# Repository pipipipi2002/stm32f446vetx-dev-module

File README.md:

# STM32F446VETx Develpoment Module

This repository contains the hardware files and firmware for basic bringup of the module as well as basic testing script.

- [Interactive BOM](https://pipipipi2002.github.io/stm32f446vetx-dev-module/hardware/STM32F446VE-Module/output/interactive_bom.html)

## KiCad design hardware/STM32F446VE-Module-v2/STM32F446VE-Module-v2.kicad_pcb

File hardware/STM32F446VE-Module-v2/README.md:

# Changelog from V1
- Flip CAN_RX and CAN_TX to TCAN332GD

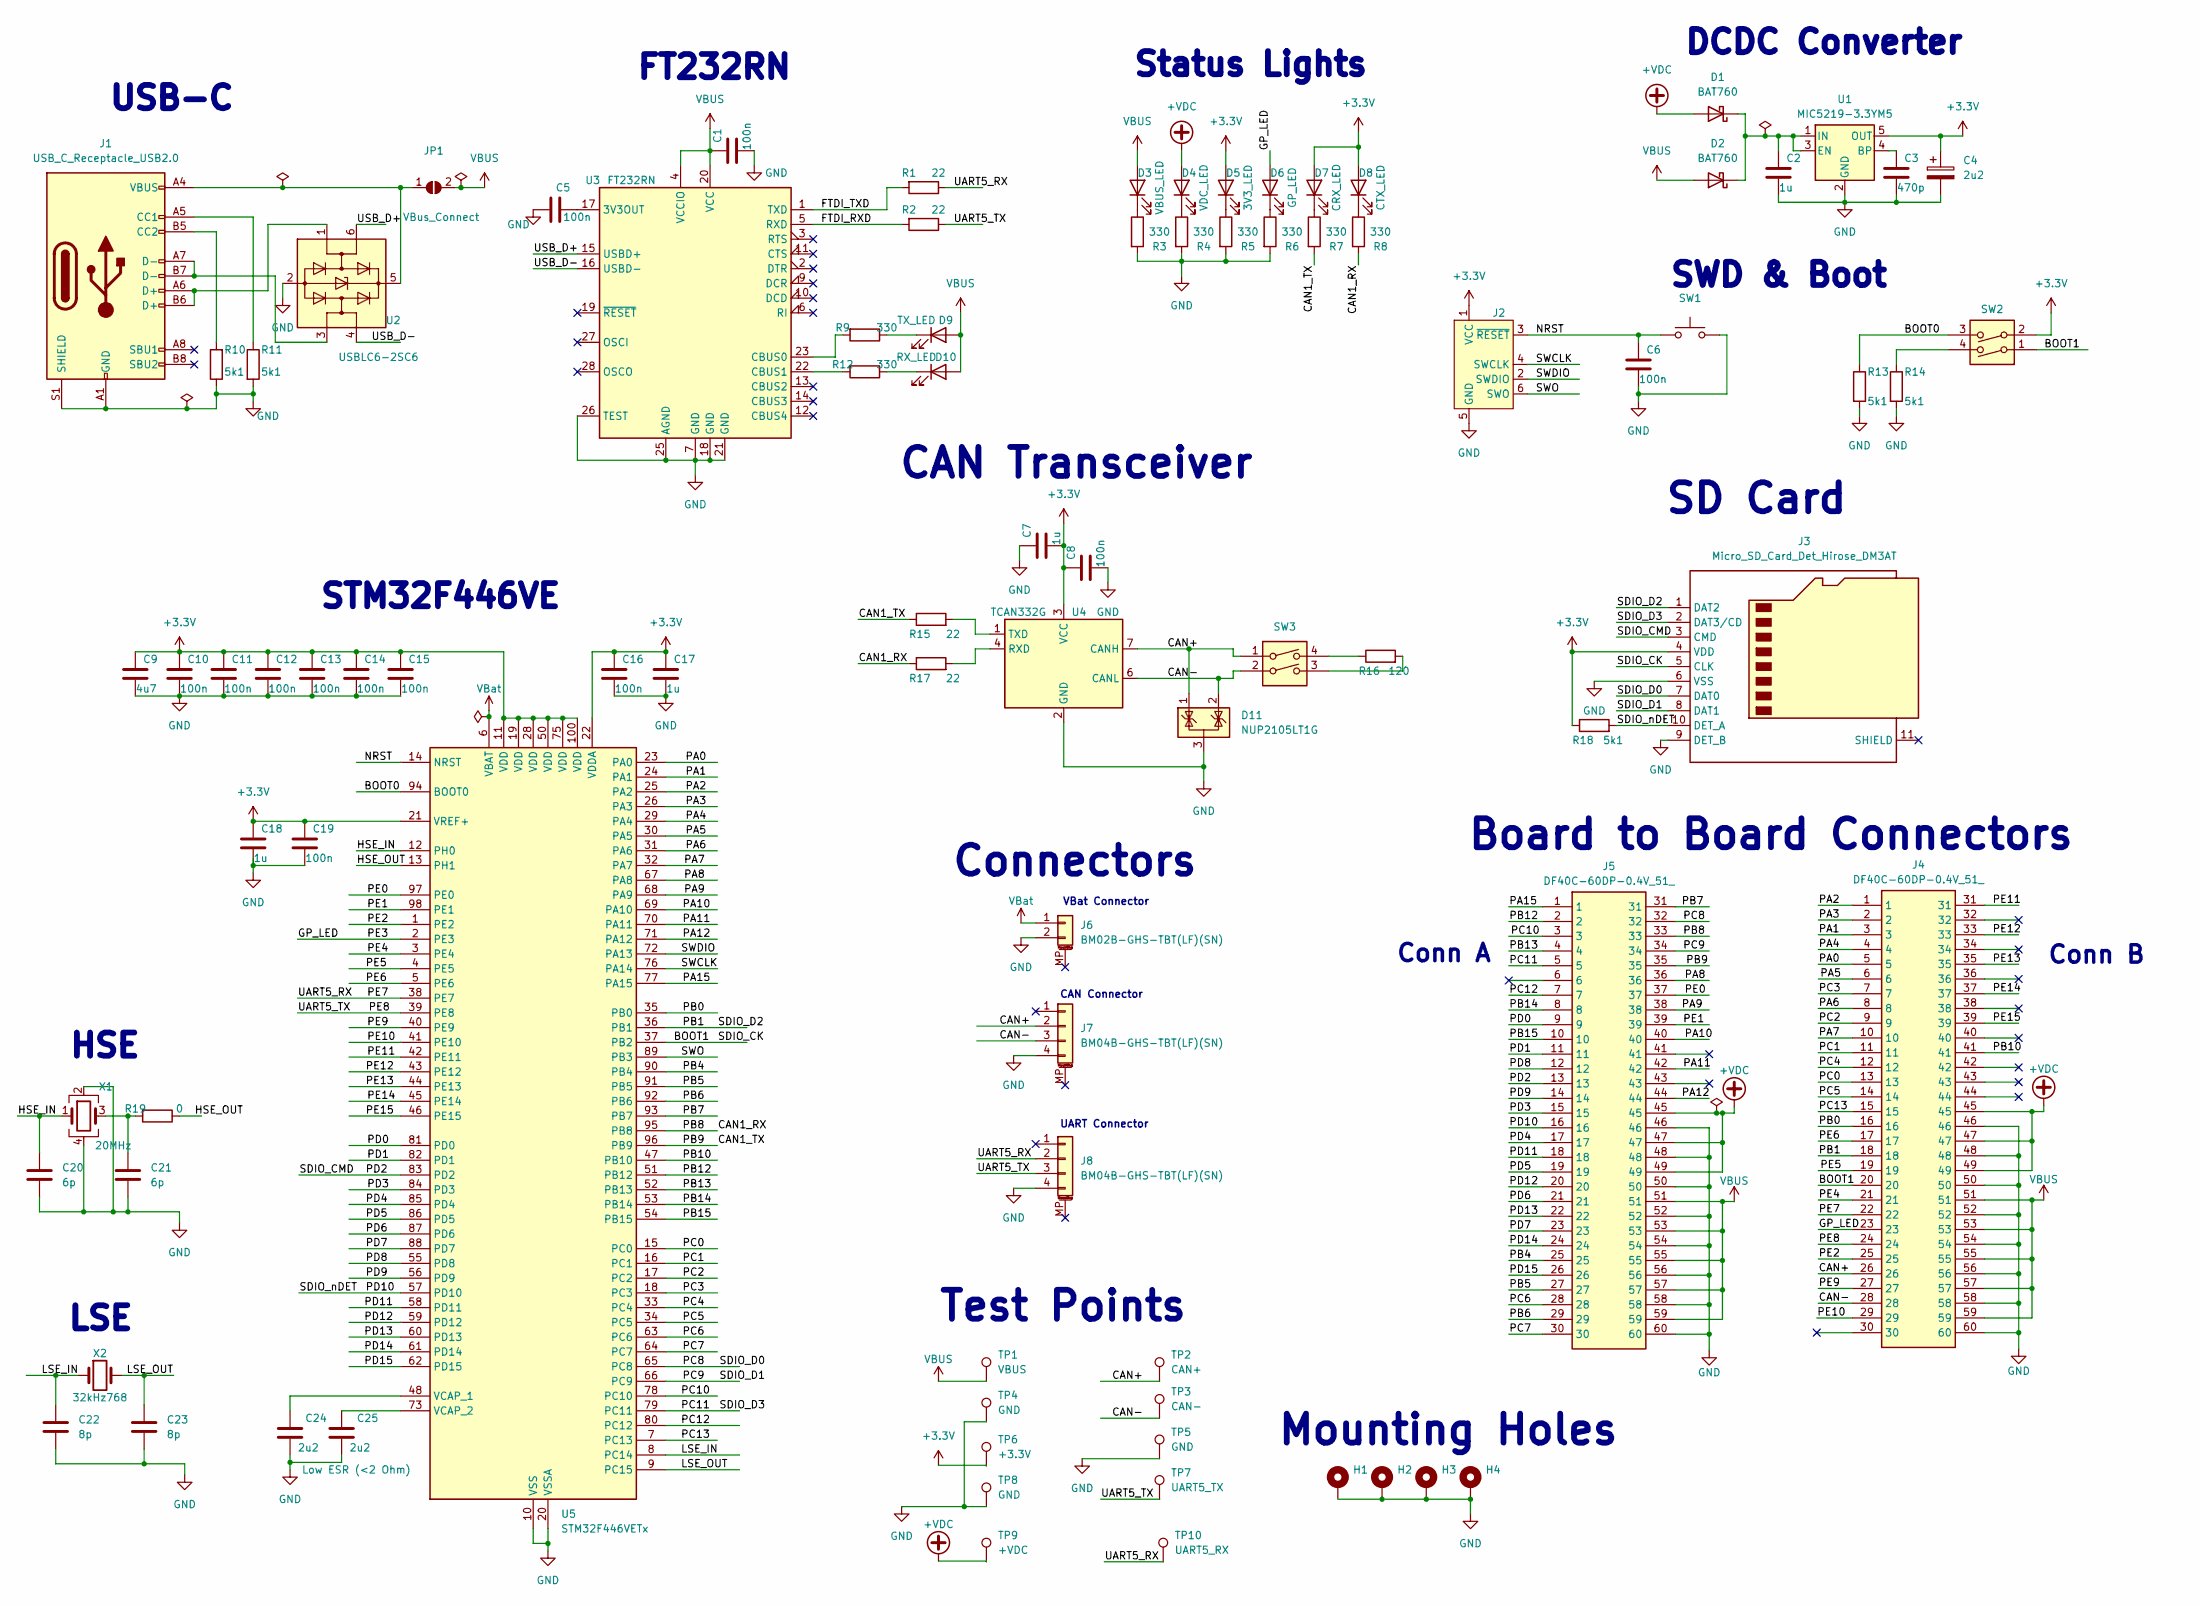
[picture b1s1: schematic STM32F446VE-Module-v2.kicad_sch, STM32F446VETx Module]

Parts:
C1, C5, C6, C8, C10, C11, C12, C13, C14, C15, C16, C19: 100n; C_0603_1608Metric; JLCPCB C1591
C2, C7, C17, C18: 1u; C_0603_1608Metric; JLCPCB C5673
C3: 470p; C_0603_1608Metric; JLCPCB C519409
C4: 2u2; CP_EIA-3216-18_Kemet-A_Pad1.58x1.35mm_HandSolder; JLCPCB C600494
C9: 4u7; C_0805_2012Metric; JLCPCB C77077
C20, C21: 6p; C_0603_1608Metric; JLCPCB C130125
C22, C23: 8p; C_0603_1608Metric; JLCPCB C469531
C24, C25: 2u2; C_0603_1608Metric; JLCPCB C100082
D1, D2: BAT760; D_SOD-323_HandSoldering; JLCPCB C124187
D3: VBUS_LED; LED_0603_1608Metric; JLCPCB C131281
D4: VDC_LED; LED_0603_1608Metric; JLCPCB C131281
D5: 3V3_LED; LED_0603_1608Metric; JLCPCB C131281
D6: GP_LED; LED_0603_1608Metric; JLCPCB C5274137
D7: CRX_LED; LED_0603_1608Metric; JLCPCB C72038
D8: CTX_LED; LED_0603_1608Metric; JLCPCB C5274137
D9: TX_LED; LED_0603_1608Metric; JLCPCB C5274137
D10: RX_LED; LED_0603_1608Metric; JLCPCB C72038
D11: NUP2105LT1G; SOT-23; JLCPCB C14486
H1, H2, H3, H4: MountingHole_Pad; MountingHole_2.7mm_M2.5_Pad_Via
J1: USB_C_Receptacle_USB2.0; USB_C_Receptacle_GCT_USB4105-xx-A_16P_TopMnt_Horizontal; JLCPCB C3020560
J2: Conn_ARM_SWD_TagConnect_TC2030; Tag-Connect_TC2030-IDC-FP_2x03_P1.27mm_Vertical
J3: Micro_SD_Card_Det_Hirose_DM3AT; microSD_HC_Hirose_DM3D-SF; JLCPCB C719027
J4, J5: DF40C-60DP-0.4V_51_; Mouser Part Number 798-DF40C60DP0.4V51
J6: BM02B-GHS-TBT(LF)(SN); JST_GH_BM02B-GHS-TBT_1x02-1MP_P1.25mm_Vertical; JLCPCB C161690
J7, J8: BM04B-GHS-TBT(LF)(SN); JST_GH_BM04B-GHS-TBT_1x04-1MP_P1.25mm_Vertical; JLCPCB C161692
JP1: VBus_Connect; SolderJumper-2_P1.3mm_Open_TrianglePad1.0x1.5mm
R1, R2, R15, R17: 22; R_0603_1608Metric; JLCPCB C491194
R3, R4, R5, R6, R7, R8, R9, R12: 330; R_0603_1608Metric; JLCPCB C441887
R10, R11, R13, R14, R18: 5k1; R_0603_1608Metric; JLCPCB C105580
R16: 120; R_0603_1608Metric; JLCPCB C114640
R19: 0; R_0603_1608Metric_Pad0.98x0.95mm_HandSolder; JLCPCB C122704
SW1: SW_Push; SW_Push_1P1T_NO_Vertical_Wuerth_434133025816; JLCPCB C5504987
SW2, SW3: SW_DIP_x02; 218-2LPSTRF; JLCPCB C314498
TP1: VBUS; TestPoint_Pad_D1.5mm
TP2: CAN+; TestPoint_Pad_D1.5mm
TP3: CAN-; TestPoint_Pad_D1.5mm
TP4, TP5, TP8: GND; TestPoint_Pad_D1.5mm
TP6: +3.3V; TestPoint_Pad_D1.5mm
TP7: UART5_TX; TestPoint_Pad_D1.5mm
TP9: +VDC; TestPoint_Pad_D1.5mm
TP10: UART5_RX; TestPoint_Pad_D1.5mm
U1: MIC5219-3.3YM5; SOT-23-5; JLCPCB C29613
U2: USBLC6-2SC6; SOT-23-6; JLCPCB C7519
U3: FT232RN; SSOP-28_5.3x10.2mm_P0.65mm; JLCPCB C5246810
U4: TCAN332G; SOIC-8_3.9x4.9mm_P1.27mm; JLCPCB C191010
U5: STM32F446VETx; LQFP-100_14x14mm_P0.5mm; JLCPCB C91929
X1: 20MHz; Crystal_SMD_3225-4Pin_3.2x2.5mm; JLCPCB C6106563
X2: 32kHz768; Crystal_SMD_2012-2Pin_2.0x1.2mm_HandSoldering; JLCPCB C5280691

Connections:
+3.3V: C4.1, C7.2, C8.1, C9.1, C10.1, C11.1, C12.1, C13.1, C14.1, C15.1, C16.1, C17.1, C18.1, C19.1, D5.2 (A), D7.2 (A), D8.2 (A), J2.1 (VCC), J3.4 (VDD), R18.1, SW2.2, TP6.1, U1.5 (OUT), U4.3 (VCC), U5.11 (VDD), U5.19 (VDD), U5.21 (VREF+), U5.22 (VDDA), U5.28 (VDD), U5.50 (VDD), U5.75 (VDD), U5.100 (VDD)
+VDC: D1.2 (A), D4.2 (A), J4.45, J4.47, J4.49, J5.45, J5.47, J5.49, TP9.1
/BOOT0: R13.1, SW2.3, U5.94 (BOOT0)
/BOOT1: J3.5 (CLK), J4.20, SW2.1, U5.37 (PB2)
/CAN1_RX: J5.33, R8.2, R17.1, U5.95 (PB8)
/CAN1_TX: J5.35, R7.2, R15.1, U5.96 (PB9)
/CAN+: D11.1 (K), J4.26, J7.2, SW3.1, TP2.1, U4.7 (CANH)
/CAN-: D11.2 (K), J4.28, J7.3, SW3.2, TP3.1, U4.6 (CANL)
/FTDI_RXD: R2.2, U3.5 (RXD)
/FTDI_TXD: R1.2, U3.1 (TXD)
/GP_LED: D6.2 (A), J4.23, U5.2 (PE3)
/HSE_IN: C20.1, U5.12 (PH0), X1.1
/HSE_OUT: R19.1, U5.13 (PH1)
/LSE_IN: C22.1, U5.8 (PC14), X2.1
/LSE_OUT: C23.1, U5.9 (PC15), X2.2
/NRST: C6.1, J2.3 (~RESET), SW1.1, U5.14 (NRST)
/PA0: J4.5, U5.23 (PA0)
/PA1: J4.3, U5.24 (PA1)
/PA2: J4.1, U5.25 (PA2)
/PA3: J4.2, U5.26 (PA3)
/PA4: J4.4, U5.29 (PA4)
/PA5: J4.6, U5.30 (PA5)
/PA6: J4.8, U5.31 (PA6)
/PA7: J4.10, U5.32 (PA7)
/PA8: J5.36, U5.67 (PA8)
/PA9: J5.38, U5.68 (PA9)
/PA10: J5.40, U5.69 (PA10)
/PA11: J5.42, U5.70 (PA11)
/PA12: J5.44, U5.71 (PA12)
/PA15: J5.1, U5.77 (PA15)
/PB0: J4.16, U5.35 (PB0)
/PB1: J3.1 (DAT2), J4.18, U5.36 (PB1)
/PB4: J5.25, U5.90 (PB4)
/PB5: J5.27, U5.91 (PB5)
/PB6: J5.29, U5.92 (PB6)
/PB7: J5.31, U5.93 (PB7)
/PB10: J4.41, U5.47 (PB10)
/PB12: J5.2, U5.51 (PB12)
/PB13: J5.4, U5.52 (PB13)
/PB14: J5.8, U5.53 (PB14)
/PB15: J5.10, U5.54 (PB15)
/PC0: J4.13, U5.15 (PC0)
/PC1: J4.11, U5.16 (PC1)
/PC2: J4.9, U5.17 (PC2)
/PC3: J4.7, U5.18 (PC3)
/PC4: J4.12, U5.33 (PC4)
/PC5: J4.14, U5.34 (PC5)
/PC6: J5.28, U5.63 (PC6)
/PC7: J5.30, U5.64 (PC7)
/PC8: J3.7 (DAT0), J5.32, U5.65 (PC8)
/PC9: J3.8 (DAT1), J5.34, U5.66 (PC9)
/PC10: J5.3, U5.78 (PC10)
/PC11: J3.2 (DAT3/CD), J5.5, U5.79 (PC11)
/PC12: J5.7, U5.80 (PC12)
/PC13: J4.15, U5.7 (PC13)
/PD0: J5.9, U5.81 (PD0)
/PD1: J5.11, U5.82 (PD1)
/PD2: J3.3 (CMD), J5.13, U5.83 (PD2)
/PD3: J5.15, U5.84 (PD3)
/PD4: J5.17, U5.85 (PD4)
/PD5: J5.19, U5.86 (PD5)
/PD6: J5.21, U5.87 (PD6)
/PD7: J5.23, U5.88 (PD7)
/PD8: J5.12, U5.55 (PD8)
/PD9: J5.14, U5.56 (PD9)
/PD10: J3.10 (DET_A), J5.16, R18.2, U5.57 (PD10)
/PD11: J5.18, U5.58 (PD11)
/PD12: J5.20, U5.59 (PD12)
/PD13: J5.22, U5.60 (PD13)
/PD14: J5.24, U5.61 (PD14)
/PD15: J5.26, U5.62 (PD15)
/PE0: J5.37, U5.97 (PE0)
/PE1: J5.39, U5.98 (PE1)
/PE2: J4.25, U5.1 (PE2)
/PE4: J4.21, U5.3 (PE4)
/PE5: J4.19, U5.4 (PE5)
/PE6: J4.17, U5.5 (PE6)
/PE7: J4.22, J8.2, R1.1, TP10.1, U5.38 (PE7)
/PE8: J4.24, J8.3, R2.1, TP7.1, U5.39 (PE8)
/PE9: J4.27, U5.40 (PE9)
/PE10: J4.29, U5.41 (PE10)
/PE11: J4.31, U5.42 (PE11)
/PE12: J4.33, U5.43 (PE12)
/PE13: J4.35, U5.44 (PE13)
/PE14: J4.37, U5.45 (PE14)
/PE15: J4.39, U5.46 (PE15)
/SWCLK: J2.4 (SWCLK), U5.76 (PA14)
/SWDIO: J2.2 (SWDIO), U5.72 (PA13)
/SWO: J2.6 (SWO), U5.89 (PB3)
/USB_D+: U2.6 (I/O1), U3.15 (USBD+)
/USB_D-: U2.4 (I/O2), U3.16 (USBD-)
GND: C1.2, C2.2, C3.2, C4.2, C5.2, C6.2, C7.1, C8.2, C9.2, C10.2, C11.2, C12.2, C13.2, C14.2, C15.2, C16.2, C17.2, C18.2, C19.2, C20.2, C21.2, C22.2, C23.2, C24.2, C25.2, D11.3 (A), H1.1, H2.1, H3.1, H4.1, J1.A1 (GND), J1.A12 (GND), J1.B1 (GND), J1.B12 (GND), J1.S1 (SHIELD), J2.5 (GND), J3.6 (VSS), J3.9 (DET_B), J4.46, J4.48, J4.50, J4.52, J4.54, J4.56, J4.58, J4.60, J5.46, J5.48, J5.50, J5.52, J5.54, J5.56, J5.58, J5.60, J6.2, J7.4, J8.4, R3.2, R4.2, R5.2, R6.2, R10.1, R11.2, R13.2, R14.2, SW1.2, TP4.1, TP5.1, TP8.1, U1.2 (GND), U2.2 (GND), U3.7 (GND), U3.18 (GND), U3.21 (GND), U3.25 (AGND), U3.26 (TEST), U4.2 (GND), U5.10 (VSS), U5.20 (VSSA), U5.27 (VSS), U5.49 (VSS), U5.74 (VSS), U5.99 (VSS), X1.2, X1.4
unnamed: C21.1, R19.2, X1.3
unnamed: C2.1, D1.1 (K), D2.1 (K), U1.1 (IN), U1.3 (EN)
unnamed: D3.1 (K), R3.1
unnamed: D4.1 (K), R4.1
unnamed: D5.1 (K), R5.1
unnamed: D6.1 (K), R6.1
unnamed: D7.1 (K), R7.1
unnamed: D8.1 (K), R8.1
unnamed: D9.1 (K), R9.1
unnamed: D10.1 (K), R12.1
unnamed: J1.A5 (CC1), R11.1
unnamed: J1.B5 (CC2), R10.2
unnamed: J1.A6 (D+), J1.B6 (D+), U2.1 (I/O1)
unnamed: J1.A7 (D-), J1.B7 (D-), U2.3 (I/O2)
unnamed: J1.A4 (VBUS), J1.A9 (VBUS), J1.B4 (VBUS), J1.B9 (VBUS), JP1.1 (A), U2.5 (VBUS)
unnamed: R14.1, SW2.4
unnamed: R16.1, SW3.4
unnamed: R16.2, SW3.3
unnamed: C3.1, U1.4 (BP)
unnamed: C5.1, U3.17 (3V3OUT)
unnamed: R9.2, U3.23 (CBUS0)
unnamed: R12.2, U3.22 (CBUS1)
unnamed: R17.2, U4.4 (RXD)
unnamed: R15.2, U4.1 (TXD)
unnamed: C24.1, U5.48 (VCAP_1)
unnamed: C25.1, U5.73 (VCAP_2)
VBUS: C1.1, D2.2 (A), D3.2 (A), D9.2 (A), D10.2 (A), J4.51, J4.53, J4.55, J4.57, J4.59, J5.51, J5.53, J5.55, J5.57, J5.59, JP1.2 (B), TP1.1, U3.4 (VCCIO), U3.20 (VCC)
VBat: J6.1, U5.6 (VBAT)

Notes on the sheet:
HSE
Board to Board Connectors
SWD & Boot
SD Card
Test Points
FT232RN
CAN Connector
LSE
VBat Connector
CAN Transceiver
USB-C
Conn A
Connectors
Conn B
STM32F446VE
Mounting Holes
Status Lights
UART Connector
DCDC Converter

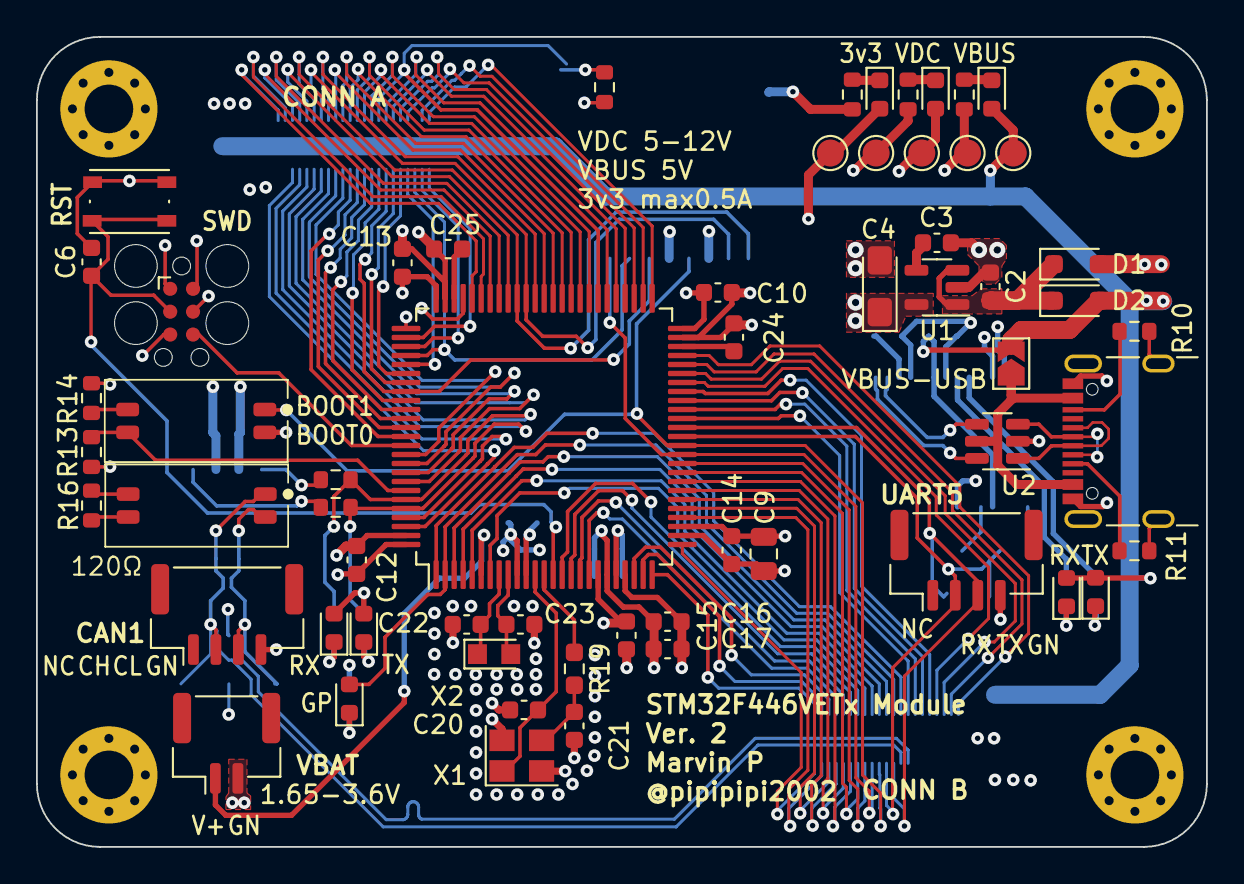
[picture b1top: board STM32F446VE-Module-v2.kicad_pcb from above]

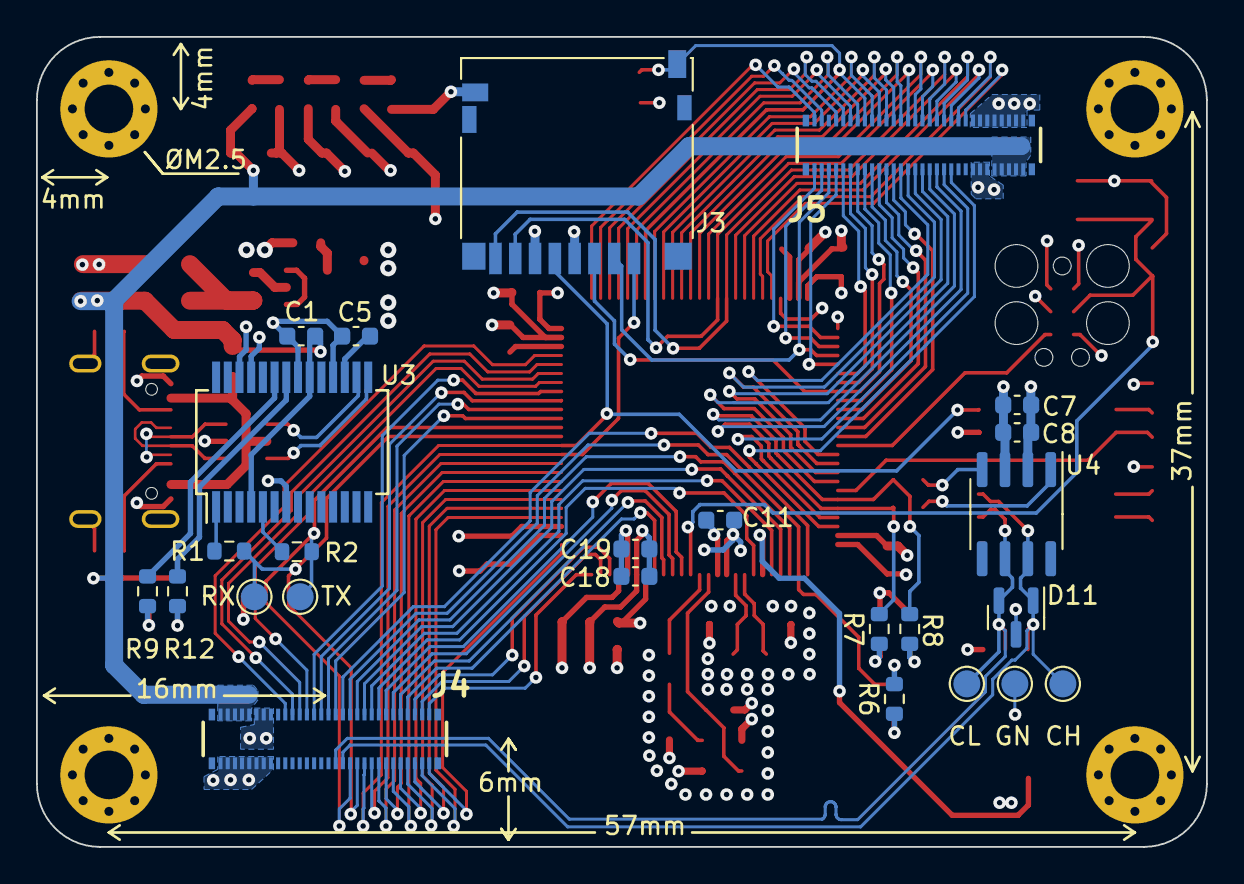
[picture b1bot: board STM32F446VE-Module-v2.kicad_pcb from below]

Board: 4 copper layers, 65.0 x 45.0 mm, 88 parts (25 on the bottom side), 120 nets.

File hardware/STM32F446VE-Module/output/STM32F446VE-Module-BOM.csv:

Comment,Designator,Footprint,LCSC
"100n","C1,C5,C6,C8,C10,C11,C12,C13,C14,C15,C16,C19","Capacitor_SMD:C_0603_1608Metric","C1591"
"1u","C2,C7,C17,C18","Capacitor_SMD:C_0603_1608Metric","C5673"
"6p","C20,C21","Capacitor_SMD:C_0603_1608Metric","C130125"
"8p","C22,C23","Capacitor_SMD:C_0603_1608Metric","C469531"
"2u2","C24,C25","Capacitor_SMD:C_0603_1608Metric","C100082"
"470p","C3","Capacitor_SMD:C_0603_1608Metric","C519409"
"2u2","C4","Capacitor_Tantalum_SMD:CP_EIA-3216-18_Kemet-A_Pad1.58x1.35mm_HandSolder","C600494"
"4u7","C9","Capacitor_SMD:C_0805_2012Metric","C77077"
"BAT760","D1,D2","Diode_SMD:D_SOD-323_HandSoldering","C124187"
"RX_LED","D10","LED_SMD:LED_0603_1608Metric","C72038"
"NUP2105LT1G","D11","Package_TO_SOT_SMD:SOT-23","C14486"
"VBUS_LED","D3","LED_SMD:LED_0603_1608Metric","C131281"
"VDC_LED","D4","LED_SMD:LED_0603_1608Metric","C131281"
"3V3_LED","D5","LED_SMD:LED_0603_1608Metric","C131281"
"GP_LED","D6","LED_SMD:LED_0603_1608Metric","C5274137"
"CRX_LED","D7","LED_SMD:LED_0603_1608Metric","C72038"
"CTX_LED","D8","LED_SMD:LED_0603_1608Metric","C5274137"
"TX_LED","D9","LED_SMD:LED_0603_1608Metric","C5274137"
"USB_C_Receptacle_USB2.0","J1","Connector_USB:USB_C_Receptacle_GCT_USB4105-xx-A_16P_TopMnt_Horizontal","C3020560"
"Micro_SD_Card_Det_Hirose_DM3AT","J3","Connector_Card:microSD_HC_Hirose_DM3D-SF","C719027"
"DF40C-60DP-0.4V_51_","J4,J5","whose_lib:DF40C-60DP-0.4V_51_","C424647"
"BM02B-GHS-TBT(LF)(SN)","J6","Connector_JST:JST_GH_BM02B-GHS-TBT_1x02-1MP_P1.25mm_Vertical","C161690"
"BM04B-GHS-TBT(LF)(SN)","J7,J8","Connector_JST:JST_GH_BM04B-GHS-TBT_1x04-1MP_P1.25mm_Vertical","C161692"
"22","R1,R2,R15,R17","Resistor_SMD:R_0603_1608Metric","C491194"
"5k1","R10,R11,R13,R14,R18","Resistor_SMD:R_0603_1608Metric","C105580"
"120","R16","Resistor_SMD:R_0603_1608Metric","C114640"
"0","R19","Resistor_SMD:R_0603_1608Metric_Pad0.98x0.95mm_HandSolder","C122704"
"330","R3,R4,R5,R6,R7,R8,R9,R12","Resistor_SMD:R_0603_1608Metric","C441887"
"SW_Push","SW1","Button_Switch_SMD:SW_Push_1P1T_NO_Vertical_Wuerth_434133025816","C5504987"
"SW_DIP_x02","SW2,SW3","whose_lib:218-2LPSTRF","C314498"
"MIC5219-3.3YM5","U1","Package_TO_SOT_SMD:SOT-23-5","C29613"
"USBLC6-2SC6","U2","Package_TO_SOT_SMD:SOT-23-6","C7519"
"FT232RN","U3","Package_SO:SSOP-28_5.3x10.2mm_P0.65mm","C5246810"
"TCAN332G","U4","Package_SO:SOIC-8_3.9x4.9mm_P1.27mm","C191010"
"STM32F446VETx","U5","Package_QFP:LQFP-100_14x14mm_P0.5mm","C91929"
"20MHz","X1","Crystal:Crystal_SMD_3225-4Pin_3.2x2.5mm","C6106563"
"32kHz768","X2","Crystal:Crystal_SMD_2012-2Pin_2.0x1.2mm_HandSoldering","C5280691"

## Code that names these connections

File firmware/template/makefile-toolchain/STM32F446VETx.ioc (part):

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Mcu.Name=STM32F446V(C-E)Tx
Mcu.Package=LQFP100
Mcu.UserName=STM32F446VETx
PA13.Mode=Trace_Asynchronous_SW
PA13.Signal=SYS_JTMS-SWDIO
PA14.Mode=Trace_Asynchronous_SW
PA14.Signal=SYS_JTCK-SWCLK
PB1.Mode=SD_4_bits_Wide_bus
PB1.Signal=SDIO_D2
PB2.Mode=SD_4_bits_Wide_bus
PB2.Signal=SDIO_CK
PB3.Mode=Trace_Asynchronous_SW
PB3.Signal=SYS_JTDO-SWO
PB8.Mode=CAN_Activate
PB8.Signal=CAN1_RX
PB9.Mode=CAN_Activate
PB9.Signal=CAN1_TX
PC11.Mode=SD_4_bits_Wide_bus
PC11.Signal=SDIO_D3
PC14-OSC32_IN.Mode=LSE-External-Oscillator
PC14-OSC32_IN.Signal=RCC_OSC32_IN
PC15-OSC32_OUT.Mode=LSE-External-Oscillator
PC15-OSC32_OUT.Signal=RCC_OSC32_OUT
PC8.Mode=SD_4_bits_Wide_bus
PC8.Signal=SDIO_D0
PC9.Mode=SD_4_bits_Wide_bus
PC9.Signal=SDIO_D1
PD10.GPIOParameters=GPIO_Label
PD10.GPIO_Label=SDIO_nDET
PD10.Signal=GPIO_Input
PD2.Mode=SD_4_bits_Wide_bus
PD2.Signal=SDIO_CMD
PE3.GPIOParameters=GPIO_Label
PE3.GPIO_Label=GP_LED
PE3.Signal=GPIO_Output
PE7.Mode=Asynchronous
PE7.Signal=UART5_RX
PE8.Mode=Asynchronous
PE8.Signal=UART5_TX
PH0-OSC_IN.Mode=HSE-External-Oscillator
PH0-OSC_IN.Signal=RCC_OSC_IN
PH1-OSC_OUT.Mode=HSE-External-Oscillator
PH1-OSC_OUT.Signal=RCC_OSC_OUT
RCC.HSE_VALUE=20000000
RCC.SYSCLKFreq_VALUE=168000000
RCC.SYSCLKSource=RCC_SYSCLKSOURCE_PLLCLK
board=custom

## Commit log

2024-01-22 Create LICENSE
2024-01-22 Rename README to README.md
2024-01-22 Prepare for fab
2024-01-29 send for fab
2024-02-01 Added generic template
2024-02-06 Create index.html for github pages
2024-02-06 Create style.css for github pages
2024-02-17 Added casing step files
2024-02-17 added 3d print files
2024-02-17 exploding view
2024-02-18 Added blinky
2024-02-19 added printf library
2024-02-21 added v2 pcb
2024-02-21 fix naming
2024-02-21 remove CAN
2024-02-22 FatFS working: write read
2024-02-23 added fatfs implementation
2024-02-23 fix pointer issues:
2024-03-07 fix trace
